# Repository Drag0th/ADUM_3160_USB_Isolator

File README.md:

# ADUM_3160_USB_Isolator
Faulty USB devices can cause serious problems, including damaging USB ports or even the motherboard. Certain devices, such as USB killers, are designed specifically to overload or destroy USB circuits. Even ordinary USB measurement tools can introduce issues, producing inaccurate readings due to ground loops or causing short circuits if there’s a fault.

A 2.5kV USB 2.0 isolator provides a simple and effective solution. It separates the data and power lines electrically, protecting both the computer and connected devices. The isolator supports full-speed USB 2.0 data transfer at 12 Mbps and provides up to 200 mA of power, making it compatible with a wide range of USB peripherals while ensuring safety and reliability.

# :file_folder: References, Links and Notes
- [ADuM3160 Datasheet](https://github.com/Drag0th/ADUM_3160_USB_Isolator/blob/main/Documentation/ADuM3160.pdf)
- [B0505S-1WR3 Datasheet](https://github.com/Drag0th/ADUM_3160_USB_Isolator/blob/main/Documentation/B_S-1WR3.pdf)

# :page_facing_up: License
*All hardware designs are released under the CERN-OHL-P v2 license.*

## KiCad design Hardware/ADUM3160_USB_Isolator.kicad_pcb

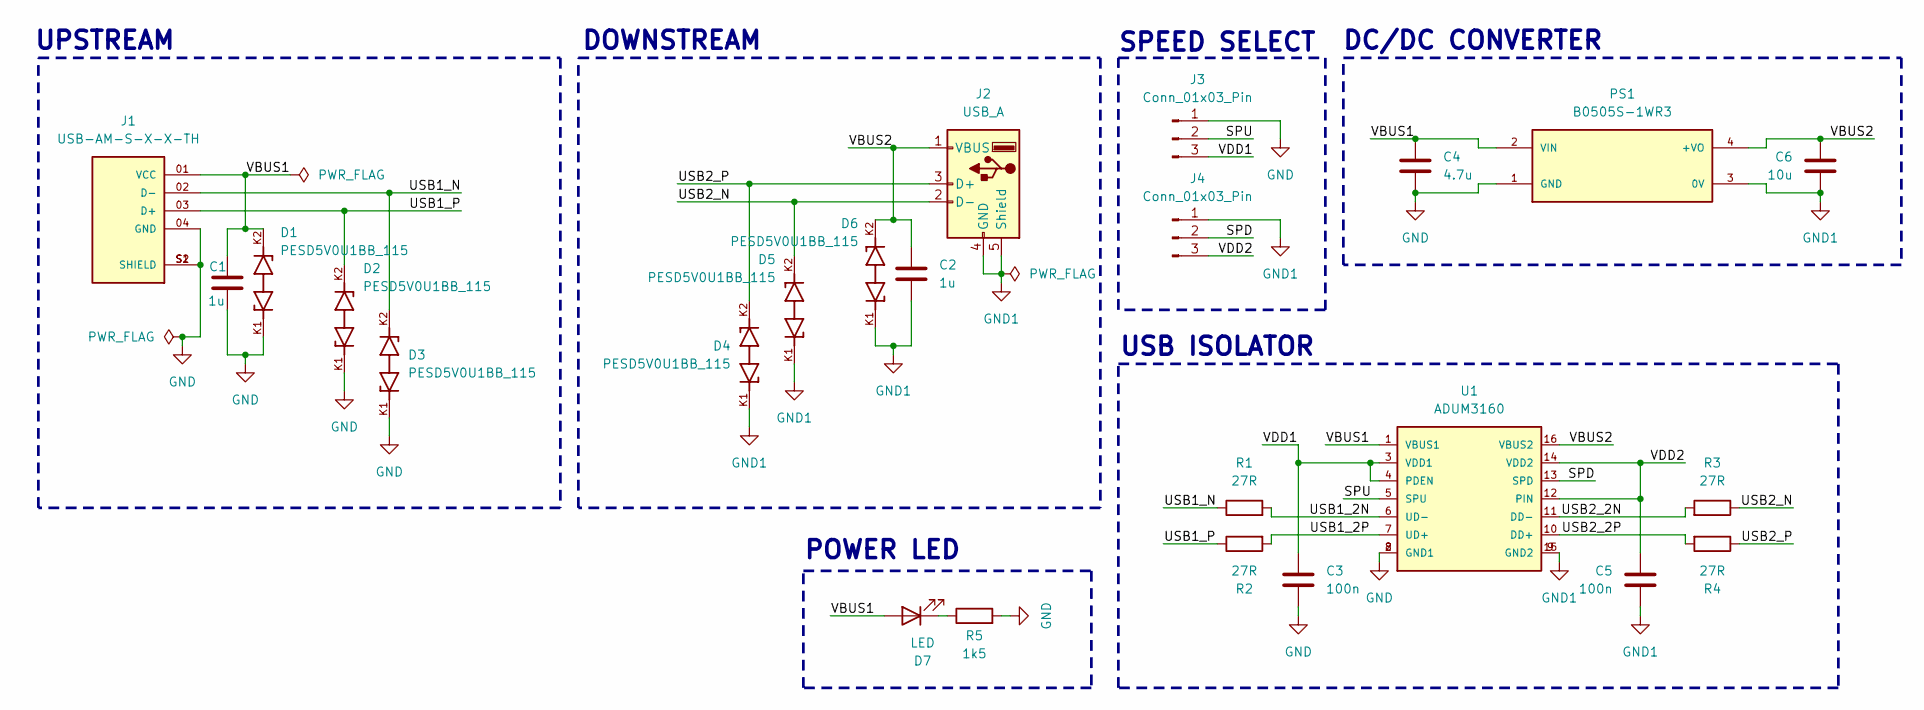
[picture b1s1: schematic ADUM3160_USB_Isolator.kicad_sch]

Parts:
C1, C2: 1u; C_0603_1608Metric_Pad1.08x0.95mm_HandSolder
C3, C5: 100n; C_0603_1608Metric_Pad1.08x0.95mm_HandSolder
C4: 4.7u; C_0603_1608Metric_Pad1.08x0.95mm_HandSolder
C6: 10u; C_0603_1608Metric_Pad1.08x0.95mm_HandSolder
D1, D2, D3, D4, D5, D6: PESD5V0U1BB_115; DIO_PESD5V0U1BB_115; PARTREV 2
D7: LED; LED_0603_1608Metric_Pad1.05x0.95mm_HandSolder
J1: USB-AM-S-X-X-TH; SAMTEC_USB-AM-S-X-X-TH; PARTREV U
J2: USB_A; USB_A_Molex_67643_Horizontal
J3, J4: Conn_01x03_Pin; PinHeader_1x03_P2.54mm_Vertical
PS1: B0505S-1WR3; CONV_B0505S-1WR3; PARTREV 2018.06.29-A/2
R1, R2, R3, R4: 27R; R_0603_1608Metric_Pad0.98x0.95mm_HandSolder
R5: 1k5; R_0603_1608Metric_Pad0.98x0.95mm_HandSolder
U1: ADUM3160; SO16L

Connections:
/SPD: J4.2, U1.13 (SPD)
/SPU: J3.2, U1.5 (SPU)
/USB1_2N: R1.2, U1.6 (UD-)
/USB1_2P: R2.2, U1.7 (UD+)
/USB1_N: D3.K2, J1.02 (D-), R1.1
/USB1_P: D2.K2, J1.03 (D+), R2.1
/USB2_2N: R3.2, U1.11 (DD-)
/USB2_2P: R4.2, U1.10 (DD+)
/USB2_N: D5.K2, J2.2 (D-), R3.1
/USB2_P: D4.K2, J2.3 (D+), R4.1
/VBUS1: C1.2, C4.2, D1.K2, D7.2 (A), J1.01 (VCC), PS1.2 (VIN), U1.1 (VBUS1)
/VBUS2: C2.2, C6.2, D6.K2, J2.1 (VBUS), PS1.4 (+VO), U1.16 (VBUS2)
/VDD1: C3.2, J3.3, U1.3 (VDD1), U1.4 (PDEN)
/VDD2: C5.2, J4.3, U1.12 (PIN), U1.14 (VDD2)
GND: C1.1, C3.1, C4.1, D1.K1, D2.K1, D3.K1, J1.04 (GND), J1.S1 (SHIELD), J1.S2 (SHIELD), J3.1, PS1.1 (GND), R5.2, U1.2 (GND1), U1.8 (GND1)
GND1: C2.1, C5.1, C6.1, D4.K1, D5.K1, D6.K1, J2.4 (GND), J2.5 (Shield), J4.1, PS1.3 (0V), U1.9 (GND2), U1.15 (GND2)
unnamed: D7.1 (K), R5.1

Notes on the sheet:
DOWNSTREAM
SPEED SELECT
USB ISOLATOR
POWER LED
DC/DC CONVERTER
UPSTREAM

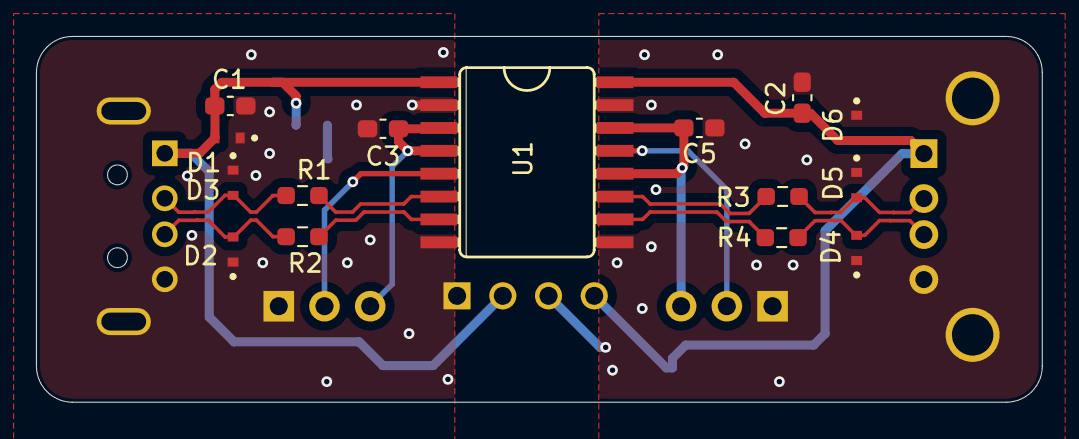
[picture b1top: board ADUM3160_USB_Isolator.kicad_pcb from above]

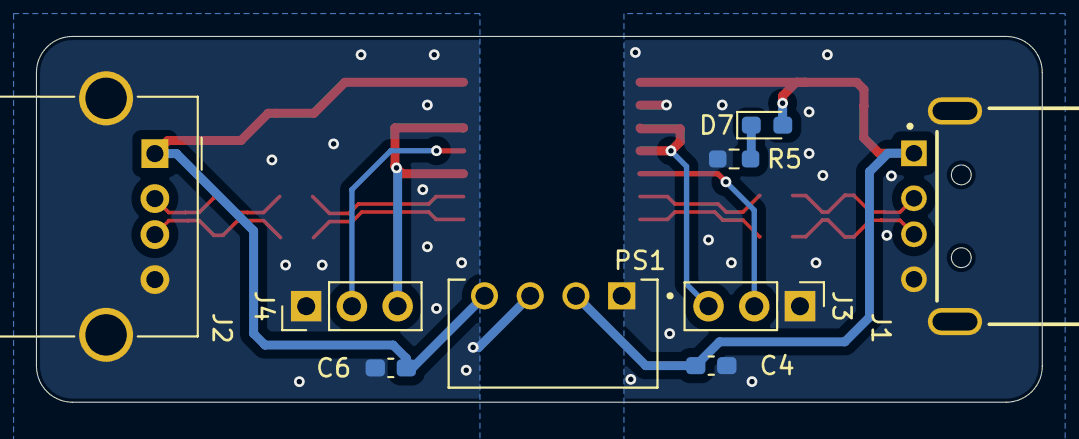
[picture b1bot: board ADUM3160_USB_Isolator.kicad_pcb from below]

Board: 2 copper layers, 55.9 x 20.3 mm, 24 parts (9 on the bottom side), 17 nets.

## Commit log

2025-10-12 Schematic update
2025-10-12 Drop files from .gitignore
2025-10-12 Footprint Update
2025-10-19 PCB & Layout update
2026-01-12 Cleanup & Repo maintain
2026-01-12 Create LICENSE
